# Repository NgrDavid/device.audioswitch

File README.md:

## Harp AudioSwitch ##

This is a multiplexer device that allows an analog input signal to be forwarded to several output channels. It allows forwarding an audio signal to a single speaker or a combination of speakers. The configuration of speakers can be predefined by software or by using a set of digital inputs.

### Key Features ###

* Configuration of up to 15 speakers (depending on the input signal strength)
* Several speakers can be activated concurrently

### Connectivity ###

* 1x stereo jack for clock sync input (CLKIN)
* 1x USB (for computer) 1x power barrel connector jack (5V only) 1x screw terminal connector for output power (GND, +5V) 1x screw terminal connector for speaker configuration (GND, DOUT0, GND, DIN0 to DIN4)

## Interface ##

The interface with the Harp board can be done through [Bonsai](https://bonsai-rx.org/) or a dedicated GUI (Graphical User Interface).

In order to use this GUI, there are some software that needs to be installed:

1 - Install the [drivers](https://bitbucket.org/fchampalimaud/downloads/downloads/UsbDriver-2.12.26.zip).

2 - Install the [runtime](https://bitbucket.org/fchampalimaud/downloads/downloads/Runtime-1.0.zip).

3 - Reboot the computer.

4 - Install the [GUI](https://bitbucket.org/fchampalimaud/downloads/downloads/Harp%20Audio%20Switch%20v1.0.0.zip).

## Licensing ##

Each subdirectory will contain a license or, possibly, a set of licenses if it involves both hardware and software.

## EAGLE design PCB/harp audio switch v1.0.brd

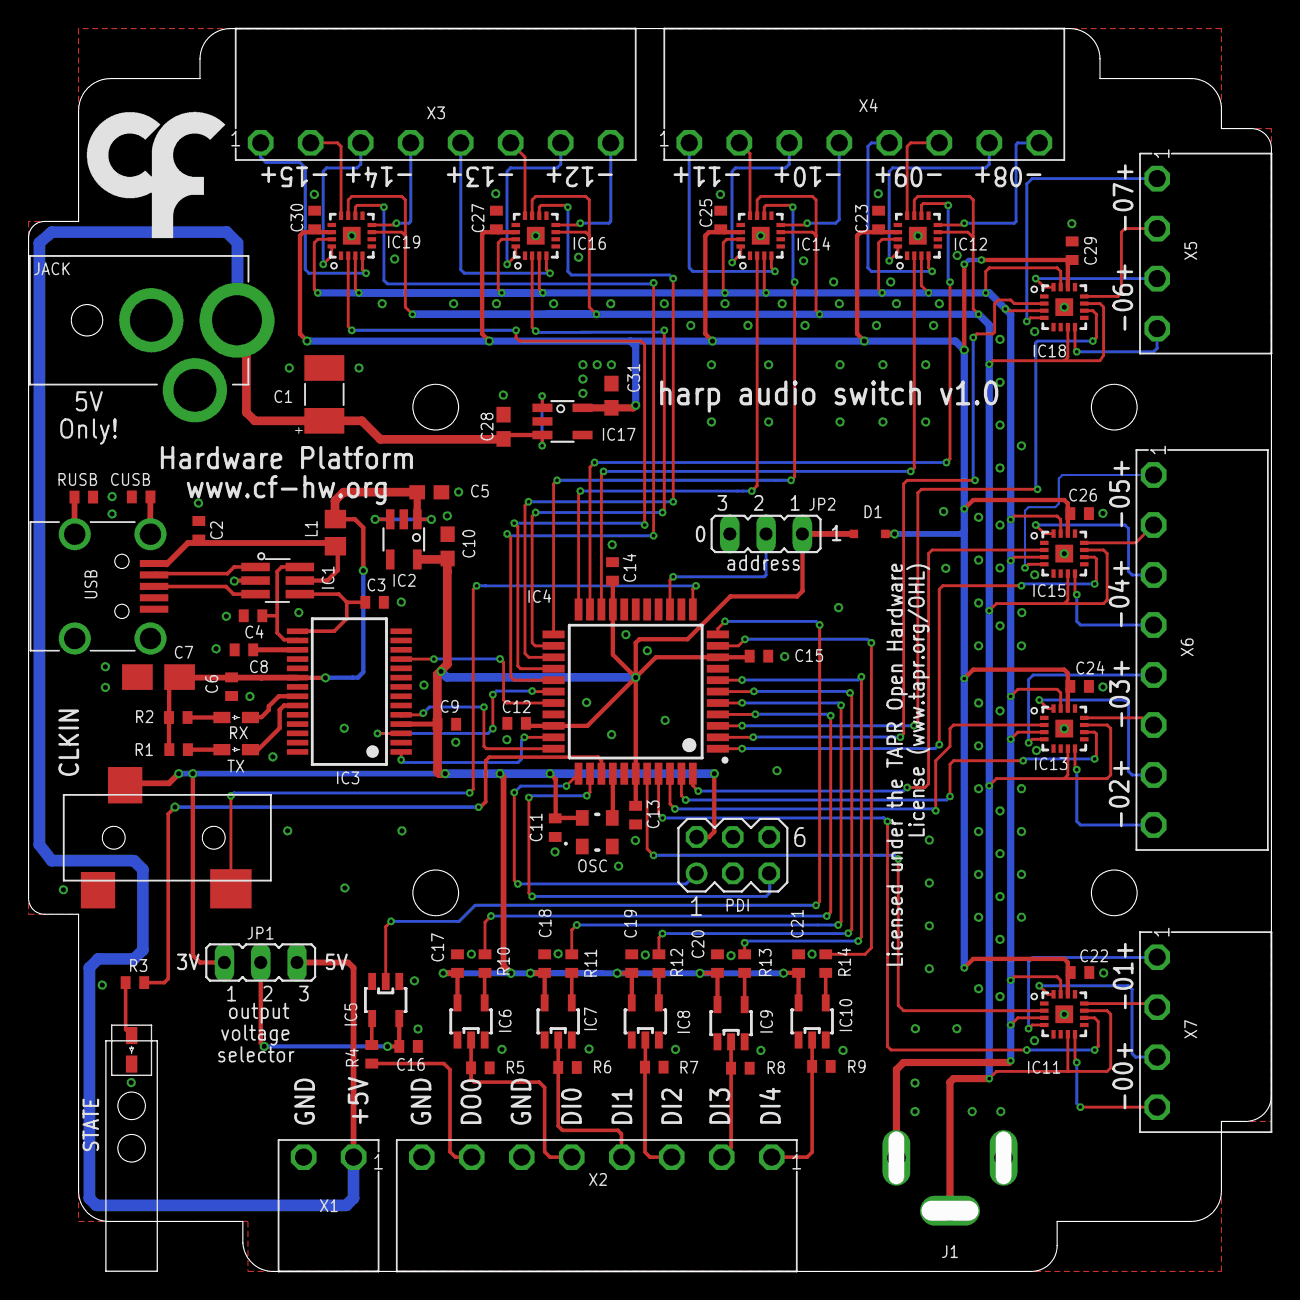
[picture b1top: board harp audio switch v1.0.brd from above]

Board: 2 copper layers, 87.0 x 87.0 mm, 89 parts (1 on the bottom side), 97 nets.

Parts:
C1: 22uF; CAP_100UF_HAND
C2, C6, C8, C9, C11, C12, C14, C15, C16, C17, C18, C19, C20, C21: 100nF; C0402
C3, C4: 47pF; C0402
C5, C10, C28, C31: 10uF; C0603
C7: 4.7uF; A/3216-18W
C13: 330nF; C0402
C22, C23, C24, C25, C26, C27, C29, C30: 10nF; C0402
CLKIN: 35RASMT2BHNTRX
CUSB: 4.7nF; C0402
D1: SOD323-R
IC1: USBLC6-2SC6; SOT23-6L
IC2, IC17: LP5907MFX-3.0; TSOT23-5
IC3: FT232RL; SSOP28
IC4: ATXMEGAxxxA4U-AU; QFP80P1200X1200X120-44N
IC5, IC6, IC7, IC8, IC9, IC10: SN74LVC1G125; SOT23-5
IC11, IC12, IC13, IC14, IC15, IC16, IC18, IC19: MAX4910; QFN16
J1: RCARCA; RCA
JACK: DC_JACKV1; DC_POWER_INPUT
JP1, JP2: JP2
L1: ???; R0805
OSC: OSCILLATOR_3.2X2.5
PDI: MA03-2
R1: 2050 NA; R0402
R2: 680 NA; R0402
R3: 68; R0402
R4, R10, R11, R12, R13, R14: 33; R0402
R5, R6, R7, R8, R9: 100k; R0402
RUSB: 1M; R0402
RX: GREEN NA; LED_HAND
STATE: GREEN; LED_HAND
TX: RED NA; LED_HAND
U$1: LED_PIPE_7513D2-L
U$3: LOGO_5
U$9: LOGO_6
USB: 240-0002-1
X1: CON_3.5MM_1X2
X2, X3, X4, X6: CON_3.5MM_1X8
X5, X7: CON_3.5MM_1X4

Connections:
5V_RAW: C5.1, C6.1, C7.+, IC2.1, IC2.3, IC3.20, L1.1, R1.2, R2.2
+5V: C1.+, C28.1, IC17.1, IC17.3, JACK.P1, JP1.3, X1.P1
ADD: IC4.14, JP2.2
CLK_SYNC: CLKIN.4, IC4.12
DI0: IC6.2, R5.2, X2.P5
DI1: IC7.2, R6.2, X2.P4
DI2: IC8.2, R7.2, X2.P3
DI3: IC9.2, R8.2, X2.P2
DI4: IC10.2, R9.2, X2.P1
DO0: R4.2, X2.P7
EN0: IC4.40, IC11.P2
EN1: IC4.41, IC11.P10
EN2: IC4.42, IC13.P2
EN3: IC4.43, IC13.P10
EN4: IC4.44, IC15.P2
EN5: IC4.1, IC15.P10
EN6: IC4.2, IC18.P2
EN7: IC4.3, IC18.P10
EN8: IC4.20, IC12.P2
EN9: IC4.21, IC12.P10
EN10: IC4.22, IC14.P2
EN11: IC4.23, IC14.P10
EN12: IC4.24, IC16.P2
EN13: IC4.25, IC16.P10
EN14: IC4.26, IC19.P2
EN15: IC4.27, IC19.P10
FT_CTS: IC3.11, IC4.29
FT_RTS: IC3.3, IC4.28
FT_RXD: IC3.5, IC4.33
FT_TXD: IC3.1, IC4.32
GND: C1.-, C2.2, C3.2, C4.2, C5.2, C6.2, C7.-, C8.2, C9.2, C10.2, C11.2, C12.2, C13.2, C14.2, C15.2, C16.2, C17.2, C18.2, C19.2, C20.2, C21.2, C22.2, C23.2, C24.2, C25.2, C26.2, C27.2, C28.2, C29.2, C30.2, C31.2, CLKIN.5, CUSB.2, IC1.P$2, IC2.2, IC3.7, IC3.18, IC3.21, IC3.25, IC3.26, IC4.8, IC4.18, IC4.30, IC4.38, IC5.1, IC5.3, IC6.1, IC6.3, IC7.1, IC7.3, IC8.1, IC8.3, IC9.1, IC9.3, IC10.1, IC10.3, IC11.EP, IC11.P6, IC12.EP, IC12.P6, IC13.EP, IC13.P6, IC14.EP, IC14.P6, IC15.EP, IC15.P6, IC16.EP, IC16.P6, IC17.2, IC18.EP, IC18.P6, IC19.EP, IC19.P6, JACK.P2, JACK.P3, JP2.3, OSC.P$2, PDI.6, R5.1, R6.1, R7.1, R8.1, R9.1, RUSB.2, STATE.K, USB.P$5, X1.P2, X2.P6, X2.P8
IN0: IC4.4, R10.2
IN1: IC4.5, R11.2
IN2: IC4.6, R12.2
IN3: IC4.7, R13.2
IN4: IC4.10, R14.2
IN_SPK_N: IC11.P7, IC11.P11, IC12.P7, IC12.P11, IC13.P7, IC13.P11, IC14.P7, IC14.P11, IC15.P7, IC15.P11, IC16.P7, IC16.P11, IC18.P7, IC18.P11, IC19.P7, IC19.P11, J1.P1
IN_SPK_P: IC11.P3, IC11.P15, IC12.P3, IC12.P15, IC13.P3, IC13.P15, IC14.P3, IC14.P15, IC15.P3, IC15.P15, IC16.P3, IC16.P15, IC18.P3, IC18.P15, IC19.P3, IC19.P15, J1.P2
unnamed: IC5.4, R4.1
unnamed: IC7.4, R11.1
unnamed: IC6.4, R10.1
unnamed: IC8.4, R12.1
unnamed: IC9.4, R13.1
unnamed: IC10.4, R14.1
unnamed: R3.1, STATE.A
unnamed: C8.1, IC3.17
unnamed: C2.1, IC1.P$5, L1.2, USB.P$1
unnamed: IC1.P$1, USB.P$2
unnamed: R2.1, RX.A
unnamed: IC3.23, TX.K
unnamed: IC3.22, RX.K
unnamed: IC1.P$3, USB.P$3
unnamed: CUSB.1, USB.SHIELD_4
unnamed: RUSB.1, USB.SHIELD_1
unnamed: R1.1, TX.A
OSC2: IC4.37, OSC.P$3
OUT0: IC4.11, IC5.2
OUT_SPK0_N: IC11.P8, X7.P4
OUT_SPK0_P: IC11.P16, X7.P3
OUT_SPK1_N: IC11.P12, X7.P2
OUT_SPK1_P: IC11.P4, X7.P1
OUT_SPK2_N: IC13.P8, X6.P8
OUT_SPK2_P: IC13.P16, X6.P7
OUT_SPK3_N: IC13.P12, X6.P6
OUT_SPK3_P: IC13.P4, X6.P5
OUT_SPK4_N: IC15.P8, X6.P4
OUT_SPK4_P: IC15.P16, X6.P3
OUT_SPK5_N: IC15.P12, X6.P2
OUT_SPK5_P: IC15.P4, X6.P1
OUT_SPK6_N: IC18.P8, X5.P4
OUT_SPK6_P: IC18.P16, X5.P3
OUT_SPK7_N: IC18.P12, X5.P2
OUT_SPK7_P: IC18.P4, X5.P1
OUT_SPK8_N: IC12.P8, X4.P8
OUT_SPK8_P: IC12.P16, X4.P7
OUT_SPK9_N: IC12.P12, X4.P6
OUT_SPK9_P: IC12.P4, X4.P5
OUT_SPK10_N: IC14.P8, X4.P4
OUT_SPK10_P: IC14.P16, X4.P3
OUT_SPK11_N: IC14.P12, X4.P2
OUT_SPK11_P: IC14.P4, X4.P1
OUT_SPK12_N: IC16.P8, X3.P8
OUT_SPK12_P: IC16.P16, X3.P7
OUT_SPK13_N: IC16.P12, X3.P6
OUT_SPK13_P: IC16.P4, X3.P5
OUT_SPK14_N: IC19.P8, X3.P4
OUT_SPK14_P: IC19.P16, X3.P3
OUT_SPK15_N: IC19.P12, X3.P2
OUT_SPK15_P: IC19.P4, X3.P1
PDI-CLK: IC4.35, PDI.5
PDI-DATA: IC4.34, PDI.1
STATE: IC4.36, R3.2
USBDM: C4.1, IC1.P$6, IC3.16
USBDP: C3.1, IC1.P$4, IC3.15
VCC: C22.1, C23.1, C24.1, C25.1, C26.1, C27.1, C29.1, C30.1, C31.1, D1.A, IC11.P14, IC12.P14, IC13.P14, IC14.P14, IC15.P14, IC16.P14, IC17.5, IC18.P14, IC19.P14
VCCIO: C9.1, C10.1, C11.1, C12.1, C13.1, C14.1, C15.1, C17.1, C18.1, C19.1, C20.1, C21.1, CLKIN.1, D1.C, IC2.5, IC3.4, IC4.9, IC4.19, IC4.31, IC4.39, IC6.5, IC7.5, IC8.5, IC9.5, IC10.5, JP1.1, JP2.1, OSC.P$4, PDI.2
VDD_OUT: C16.1, IC5.5, JP1.2

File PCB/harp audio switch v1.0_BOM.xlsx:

| Part(s) | Quantity | Description | Distributor | Part. No.
 | IC1 | 1 | ESD Protection Low Cap | Mouser | 511-USBLC6-2SC6Y
 | IC2, IC17 | 2 | LDO 250mA Ultra-Lo Noise LDO Reg 3V | Mouser | 595-LP5907MFX-3.0NPB
 | IC3 | 1 | IC USB USB to Serial UART Enhanced IC SSOP-28 | Mouser | 895-FT232RL
 | IC4 | 1 | Microcontroladores de 8 bits - MCU 44TQFP, IND TEMP GREEN, 1.6-3.6V | Mouser | 556-ATXMEGA128A4U-AU
 | IC5, IC6, IC7, IC8, IC9, IC10 | 6 | Buffers e line drivers 1.65-5.5V Single Non-Inverting TTL | Mouser | 863-M74VHC1GT50DTT1G
 | IC10, IC11, IC12, IC13, IC14, IC15, IC16, IC18 | 8 | CIs de Chave Analógica Quad-SPDT Clickless Audio Switch | Mouser | 700-MAX4910ETE
 |  | 0 | LDO 250mA Ultra-Lo Noise LDO Reg | Mouser | 595-LP5907MFX-2.8NPB
 | C3, C4 | 2 | CAP CER 47pF 50V ±5% C0G 0402 | Mouser | 77-VJ0402A470JXACBC
 | CUSB | 1 | CAP CER 4.7nF 100V ±10% X7R 0402 | Mouser | 81-GRM155R72A472KA01
 | C22, C23, C24, C25, C26, C27, C29, C30 | 8 | CAP CER 10nF 10V ±10% X5R 0402 | Mouser | 81-GRM155R61A103KA1D
 | C2, C6, C8, C9, C11, C12, C14, C15, C16, C17, C18, C19, C20, C21 | 14 | CAP CER 100nF 10V X5R 0402 | REEL | REEL
 | C13 | 1 | CAP CER 0.33uF 10V ±10% X5R 0402 | Mouser | GRM155R61A334KE15D
 | C7 | 1 | CAP TAN 4.7uF 16V ±10% 1206 | Mouser | 80-T491A475K16AT7280
 | C5, C10, C28, C31 | 4 | CAP CER 10uF 10V ±10% X5R 0603 | Mouser | 81-GRM188R61A106KE9D
 | C1 | 1 | CAP TAN 22uF 20V ±10% 1210 | Mouser | 667-20TQC22MYFB
 | R4, R10, R11, R12, R13, R14 | 6 | RES SMD 33Ω 5% 0402 | Mouser | 667-ERJ-2GEJ330X
 | R3 | 1 | RES SMD 68Ω 5% 0402 | Mouser | 71-CRCW0402-68-E3
 | R5, R6, R7, R8, R9 | 5 | RES SMD 100kΩ 1% 0402 | REEL | REEL
 | RUSB | 1 | RES SMD 1MΩ 1% 0402 | Mouser | 652-CR0402FX-1004GLF
 | D1 | 1 | DIODE SCHOTTKY 30V 1A SOD323 | Mouser | 621-SDM100K30L-7
 | STATE | 1 | LED, Green, 1.6mm x 0.8mm, 566 nm, 2.1 V, 20 mA, 15 mcd | Mouser | 78-TLMP1100-GS08
 | OSC | 1 | 32MHz 10ppm | Mouser | 998-1001CI5032.0000T
 | CLKIN | 1 | SMT 3.5 STEREO REEL | Mouser | 502-35RASMT2BHNTRX
 | L1 | 1 | 40ohms 100MHz 1.5A Monolithic 0805 SMD | Mouser | 875-MI0805K400R-10
 | PDI | 1 | 6P DR UNSHRD HRD | Mouser | 649-67996-206HLF
 | J1 | 1 | Conectores de fono RCA 1 POS RA PHONO JACK | Mouser | 502-PJRAN1X1U03AUX
 | USB | 1 | UX60-MB-5S8 | Mouser | 798-UX60-MB-5S8
 | USB Cable | 1 | USB A - MINI-B 1M BLACK | Mouser | 538-88732-8602
 |  | 1 | Tubos de Luz LED CML LIGHTPIPE | Mouser | 606-7513D2-L
 | JACK | 1 | CC 2.5mm LOCKING | Mouser | 161-0725-E
 | JP1, JP2 | 2 | 3POS Gold Male | Mouser | 649-68001-203HLF
 |  | 2 | SHUNT JUMPER, 2POS | Farnell | 2396301
 | WALL ADAPTER | 1 | AC/DC Power Supply, 1 Output, 5 W, 5 V, 1 A | Farnell | 1971787
 | X1 | 1 | 20.1550M/2-E - Pluggable Terminal Block, 3.5 mm, 2 Ways, 28 AWG, 16 AWG, 1.5 mm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 | Farnell | 2575215
 | X5, X7 | 2 | 20.1550M/4-E - Pluggable Terminal Block, 3.5 mm, 4 Ways, 28 AWG, 16 AWG, 1.5 mm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 | Farnell | 2575217
 | X2, X3, X4, X6 | 4 | 20.1550M/8-E - Pluggable Terminal Block, 3.5 mm, 8 Ways, 28 AWG, 16 AWG, 1.5 mm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 | Farnell | 2575220
 |  | 1 | 20.155MH/2-E - Terminal Block, Horizontal, Header, 3.5 mm, 2 Ways, 10 A | Farnell | 2517858
 |  | 2 | 20.155MH/4-E - Terminal Block, Horizontal, Header, 3.5 mm, 4 Ways, 10 A | Farnell | 2517860
 |  | 4 | 20.155MH/8-E - Terminal Block, Horizontal, Header, 3.5 mm, 8 Ways, 10 A | Farnell | 2517863
 |  | 8 | 1110030 - Nut, Hex, M3, Nylon 6.6, Pack of 50 | Farnell | 1110030
 |  | 4 | Machine Screw, M3, 10 mm, Nylon (Polyamide), Pan Head Slotted, PK25 | Farnell | 1514410
 | Components | 106
 | Licensed under the TAPR Open Hardware License (www.tapr.org/OHL)
 | Copyright 2017 Artur Silva and Filipe Carvalho

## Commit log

2018-04-24 Initial commit.
2018-04-24 Corrected device ID to 1248.
2018-04-27 Removed bit B_EVT_DO from the bits list.
2018-04-27 Added filter to the digital inputs.
2018-04-27 Added missing EVT enable validation to some events.
2018-06-14 Removed 100 us interval between shutdown all outputs and select the new configuration.
2022-12-16 Add PCB and BOM files
2022-12-16 Add licenses
2022-12-18 refactor assets' folder structure
2022-12-23 refactor repository structure
2023-05-10 added yml file
2023-05-10 Correct masks naming
2023-05-10 Add PCB image
2023-05-10 Add Interface folder and files
2023-05-10 Add Generator folder and files
2023-05-15 Updated interface auto generation files
2023-07-27 Refactor for consistency
2023-08-09 update device.yml with channels bitmask
2023-08-09 update yml with register renaming
2023-08-10 update autogen interface files
2023-08-10 Add .gitignore to Firmware and Hardware
2023-08-10 Remove file extension
2023-08-11 Updated firmware version.
2023-08-11 Updated dates.
2023-08-11 Replaced harp core 1.4 with 1.13.
2023-08-19 Reduce PCB image dimensions
2023-08-19 Move .gitignore
2023-08-19 Add Mechanical folder + license
2023-09-14 Update core start parameters and fw version
2023-09-14 Update device.yml firmware version
2024-11-13 Update device schema source
2024-11-13 Update AudioSwitch csproj
2024-11-13 Update generators and regenerate interface
2024-11-21 add missing asset for device interface
2025-05-16 Create basic CI/CD for interface package

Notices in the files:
PCB/harp audio switch v1.0.brd:
Copyright 2018 Artur Silva and Filipe Carvalho
